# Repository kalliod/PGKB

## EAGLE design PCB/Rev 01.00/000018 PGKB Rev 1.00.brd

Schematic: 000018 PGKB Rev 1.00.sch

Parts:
C1, C2: C0805_18PF_50V_NP0; CAPC2012X160
C3, C4, C7, C8, C20, C46: C0805_1UF_50V_X5R; CAPC2012X160
C5, C9, C19, C21, C29, C30, C31, C33, C34, C44, C48: C0603_100NF_50V_X7R; CAPC1608X90
C6: C0805_10NF_50V_X7R; CAPC2012X160
C10, C11, C13, C14, C15, C16, C17, C18, C22, C23, C24, C25, C26, C27: C0805_1NF_50V_X7R; CAPC2012X160
C12: C0805_4.7UF_25V_X5R; CAPC2012X160
C28, C32: C1206_10UF_16V_Y5V; CAPC3216X200
D1: DIODE_TVS_5V_BI_824015; SOP95P280X120-6N
D2: DIODE_TVS_5V_SMAJ5.0A; DIOC530X280X230_SMA_A
D3: LED_0603_GREEN_CLEAR_APTD1608CGCK; LEDM1608X80N_DOME
D4, D27: LED_0603_AMBER_DIFF_LOQ976-PS-25; LEDM1608X80N
ENCLOSURE1: ENCLOSURE_BOPLA_BOP-500-9005-TOP; ENCLOSURE_BOPLA_BOP-500-9005
FB1, FB2, FB3, FB4, FB6: FERRITE_0805_0A5; RESC2012X50
FIDUCIAL1, FIDUCIAL2, FIDUCIAL3, FIDUCIAL4, FIDUCIAL5, FIDUCIAL6: FIDUCIAL
H1, H2, H3, H4, H5, H6, H7, H8: SWITCH_CAP_DSA_RELEG
L1: L_CHOKE_EXC-34CE670U; IND_CHOKE_EXC-34
LOGO2: ART_LOGO_TEXT_2.5MM-SILK; ART_LOGO_TEXT_2.5MM_SILK
R1, R7: R0805_10K_5%; RESC2012X50
R2, R3, R13, R18, R23, R25, R26, R27, R28, R29, R30: R0805_1K_1%; RESC2012X50
R4, R5: R0603_22; RESC1608X45N
R6: R0805_1M_5%; RESC2012X50
R8, R9, R10, R11, R12, R14, R15, R19, R21, R22, R31: R0805_200_1%; RESC2012X50
R16: R0402_DNP; RESC1005X35N
R17, R20: R0805_3K3_1%; RESC2012X50
R24, R32, R33: R0603_0; RESC1608X45N
S1, S3, S4, S5, S6, S7, S8, S9: SWITCH_BUTTON_MX1A-C1NW; SWITCH_BUTTON_CHERRY_MX
S10: SWITCH_MOM_SPST_FSM4JSMA; SWITCH_BUTTON_TE_FSM4JSMA
TP1, TP2, TP3, TP5, TP7, TP15, TP16, TP17: PAD_TEST_POINT-2.5/0.7_A; TEST_POINT_2.5MM_0.7HOLE_1SIDE
U1: IC_MCU_ATMEGA32U4-AU; QFP80P1000X1000X120-44R_N
U2: IC_MEM_FLASH_AT45DB321E; SOP127P800X175-8
U3: IC_REG_3V3_1A_NCP1117LPST33T3G; SOT223
U4, U5, U6: IC_LEVEL_SHIFTER_SN74LVC2T45; SOP65P400X130-8
X1: CON_USB_MICROB_UJ2-MIBH-4-SMT-TR-MAN; CON_USB_MICROB_UJ2-MIBH-4-SMT-TR_MAN
X2: CON_PROG_AVR_ISP-OFFSET_1X06; CON_PINHD_1X06_TH_OFFSET
X3: CON_1X04_TH_OFFSET_PADS-SILK; 1X04_TH_OFFSET
X4, X5, X6, X9, X10, X12, X17, X18: HOL_3.2/6.0_NP; MTG_NP_M3_320X600
X11: CON_MICROSD_MOLEX_5033981892-M; CON_MICROSD_MOLEX_5033981892_M
X13: PAD_TEST_GROUND_HOOK; PAD_GND_HOOK_M
X14: CON_CLAMP_PTSM_1X04_H_SMD; CON_PHOENIX_CONTACT_1702474
X15: CON_CLAMP_PTSM_1X08_H_SMD; CON_PHOENIX_CONTACT_1771088
Y1: OSC_CRYSTAL_16M_ABLS-16.000MHZ-B4-T-HC49; OSC_CRYSTAL_HC49/US

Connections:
!CS!_FLASH_3V3: U2.4 (!CS!), U6.6 (B2)
!CS!_FLASH_5V: U1.31 (PC6(OC3A/!OC4A!)), U6.3 (A2)
!CS!_SD_3V3: U6.7 (B1), X11.2 (CD/DAT3)
!CS!_SD_5V: U1.25 (PD4(ICP1/ADC8)), U6.2 (A1)
!RESET: R1.P$1 (1), S10.1, TP5.P$1, U1.13 (!RESET), X2.5 (RST), X3.1
!RESET!_3V3: R32.P$1 (1), U2.3 (!RESET!)
+3V3: C9.P$2 (2), C19.P$2 (2), C20.P$2 (2), C28.P$1 (1), C29.P$1 (1), C31.P$1 (1), C34.P$1 (1), C44.P$1 (1), C46.P$2 (2), R32.P$2 (2), R33.P$2 (2), TP3.P$1, U2.6 (V+), U3.2 (VO), U3.4 (VO), U4.8 (VB), U5.8 (VB), U6.8 (VB), X11.4 (VDD)
+5V: C3.P$1 (1), C4.P$1 (1), C5.P$1 (1), C6.P$1 (1), C12.P$1 (1), C21.P$2 (2), C30.P$2 (2), C32.P$1 (1), C33.P$2 (2), C48.P$1 (1), D1.5 (V+), D2.C (K), FB1.P$2 (2), FB3.P$1 (1), FB6.P$2 (2), R1.P$2 (2), R16.P$2 (2), R17.P$2 (2), R20.P$2 (2), R23.P$2 (2), TP7.P$1, U1.2 (UVCC), U1.14 (VCC), U1.34 (VCC1), U3.3 (VI), U4.1 (VA), U4.5 (DIR), U5.1 (VA), U6.1 (VA), U6.5 (DIR)
AD0: C22.P$1 (1), R25.P$2 (2), U1.36 (PF7(ADC7(TDI))
AD1: C23.P$1 (1), R26.P$2 (2), U1.37 (PF6(ADC6/TDO))
AD4: C24.P$1 (1), R27.P$2 (2), U1.38 (PF5(ADC5/TMS))
AD5: C25.P$1 (1), R28.P$2 (2), U1.39 (PF4(ADC4/TCK))
AD6: C26.P$1 (1), R29.P$2 (2), U1.40 (PF1(ADC1))
AD7: C27.P$1 (1), R30.P$2 (2), U1.41 (PF0(ADC0))
BUTTON1: C10.P$1 (1), R8.P$2 (2), U1.26 (PD6(T1/ADC9/!OC4D))
BUTTON2: C11.P$1 (1), R9.P$2 (2), U1.27 (PD7(OC4D/ADC10/T0))
BUTTON3: C13.P$1 (1), R10.P$2 (2), U1.28 (PB4(ADC11))
BUTTON4: C14.P$1 (1), R11.P$2 (2)
BUTTON5: C15.P$1 (1), R12.P$2 (2), U1.29 (PB5(OC1A/ADC12/!OC4B!))
BUTTON6: C16.P$1 (1), R14.P$2 (2), U1.30 (PB6(OC1B/OC4B/ADC13))
BUTTON7: C17.P$1 (1), R15.P$2 (2), U1.12 (PB7(OC0A/OC1C/RTS))
BUTTON8: C18.P$1 (1), R19.P$2 (2), U1.32 (PC7(ICP3/CLK0/OC4A))
CLK_3V3: TP1.P$1, U2.2 (SCK), U4.7 (B1), X11.5 (CLK)
CLK_5V: TP2.P$1, TP15.P$1, U1.9 (PB1(SCK)), U4.2 (A1), X2.3 (SCK)
GND: C1.P$2 (2), C2.P$2 (2), C3.P$2 (2), C4.P$2 (2), C5.P$2 (2), C6.P$2 (2), C7.P$2 (2), C9.P$1 (1), C10.P$2 (2), C11.P$2 (2), C12.P$2 (2), C13.P$2 (2), C14.P$2 (2), C15.P$2 (2), C16.P$2 (2), C17.P$2 (2), C18.P$2 (2), C19.P$1 (1), C20.P$1 (1), C21.P$1 (1), C22.P$2 (2), C23.P$2 (2), C24.P$2 (2), C25.P$2 (2), C26.P$2 (2), C27.P$2 (2), C28.P$2 (2), C29.P$2 (2), C30.P$1 (1), C31.P$2 (2), C32.P$2 (2), C33.P$1 (1), C34.P$2 (2), C44.P$2 (2), C46.P$1 (1), C48.P$2 (2), D2.A, D3.C (CATHODE), D4.C (CATHODE), D27.C (CATHODE), FB2.P$1 (1), FB4.P$1 (1), R7.P$2 (2), R24.P$2 (2), S1.1, S3.1, S4.1, S5.1, S6.1, S7.1, S8.1, S9.1, S10.3, U1.15 (GND), U1.23 (GND1), U1.35 (GND2), U1.43 (GND3), U2.7 (GND), U3.1 (GND), U4.4 (GND), U5.4 (GND), U5.5 (DIR), U6.4 (GND), X2.6 (GND), X3.4, X11.6 (VSS), X11.DET_LVR (LAT), X13.P$1, X13.P$2, X14.4, X15.8
GND_E: FB2.P$2 (2), X1.G1 (TAB), X1.G2 (TAB), X1.H1 (TAB), X1.H2 (TAB), X1.H3 (TAB), X1.H4 (TAB), X11.H1 (GND1), X11.H2 (GND2), X11.H3 (GND3), X11.H4 (GND4)
INTERRUPT7: R31.P$2 (2), U1.1 (PE6(INT.6/AIN0))
MISO_3V3: U2.8 (MISO), U5.7 (B1), X11.7 (DAT0)
MISO_5V: TP16.P$1, U1.11 (PB3(PDO/MISO)), U5.2 (A1), X2.1 (MISO)
MOSI_3V3: U2.1 (MOSI), U4.6 (B2), X11.3 (CMD)
MOSI_5V: TP17.P$1, U1.10 (PB2(PDI/MOSI)), U4.3 (A2), X2.4 (MOSI)
unnamed: D1.1, L1.A2, X1.D+
unnamed: D1.6, L1.B2, X1.D-
unnamed: C7.P$1 (1), FB3.P$2 (2), U1.24 (AVCC), U1.44 (AVCC1)
unnamed: D4.A (ANODE), R18.P$1 (1)
unnamed: C1.P$1 (1), R6.P$1 (1), U1.17 (XTAL1), Y1.2
unnamed: C2.P$1 (1), R6.P$2 (2), U1.16 (XTAL2), Y1.1
unnamed: C8.P$2 (2), U1.6 (UCAP)
unnamed: R2.P$2 (2), X3.2
unnamed: R3.P$2 (2), X3.3
unnamed: R7.P$1 (1), U1.33 (PE2(!HWB))
unnamed: D27.A (ANODE), R13.P$1 (1)
unnamed: R8.P$1 (1), S1.2
unnamed: R16.P$1 (1), X2.2 (VCC)
unnamed: R9.P$1 (1), S3.2
unnamed: R10.P$1 (1), S4.2
unnamed: R11.P$1 (1), S5.2
unnamed: R12.P$1 (1), S6.2
unnamed: R14.P$1 (1), S7.2
unnamed: R15.P$1 (1), S8.2
unnamed: R19.P$1 (1), S9.2
unnamed: L1.B1, R5.P$1 (1)
unnamed: L1.A1, R4.P$1 (1)
unnamed: R33.P$1 (1), U2.5 (!WP!)
unnamed: R17.P$1 (1), R21.P$1 (1), X14.1
unnamed: R20.P$1 (1), R22.P$1 (1), X14.2
unnamed: D3.A (ANODE), R23.P$1 (1)
unnamed: R24.P$1 (1), U5.6 (B2)
unnamed: FB6.P$1 (1), X15.1
unnamed: R27.P$1 (1), X15.4
unnamed: R28.P$1 (1), X15.5
unnamed: R31.P$1 (1), X14.3
unnamed: R25.P$1 (1), X15.2
unnamed: R26.P$1 (1), X15.3
unnamed: R29.P$1 (1), X15.6
unnamed: R30.P$1 (1), X15.7
RXD: R2.P$1 (1), U1.20 (PD2(INT2/RXD1))
RX_LED: R13.P$2 (2), U1.8 (PB0(SS))
SCL_5V: R21.P$2 (2), U1.18 (PD0(INT0/OC0B/SCL))
SDA_5V: R22.P$2 (2), U1.19 (PD1(INT1/SDA))
SD_DETECT: X11.DET_SW (SW)
TXD: R3.P$1 (1), U1.21 (PD3(INT3/TXD1))
TX_LED: R18.P$2 (2), U1.22 (PD5(XCK/CTS))
USB_D+: R4.P$2 (2), U1.4 (D+)
USB_D-: R5.P$2 (2), U1.3 (D-)
USB_GND: C8.P$1 (1), D1.2 (V-), FB4.P$2 (2), U1.5 (UGND), X1.GND
USB_ID: X1.ID
USB_VBUS: FB1.P$1 (1), U1.7 (VBUS), X1.VBUS (V+)

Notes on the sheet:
Fiducials
Artwork
Mounting screws (optional)
Ground loop
microSD card slot
Programming connectors
!RESET! signal
3V3 regulation
USB connector
SPI bus level shifting
GND
Microcontroller
USB data LED
Buttons
Flash memory chip
External I2C connector
// D2 SDA
// D3 SCL
// A0
// A1
// A4
// A5
// A6
// A7
// USB data LED
Power LED
ADC
Use internal 2.56 V ref
// D7
// D0 RX
// D1 TX
// D4
// D12
// D13
// D6
// D8
// D9
// D10
// D11
// D5

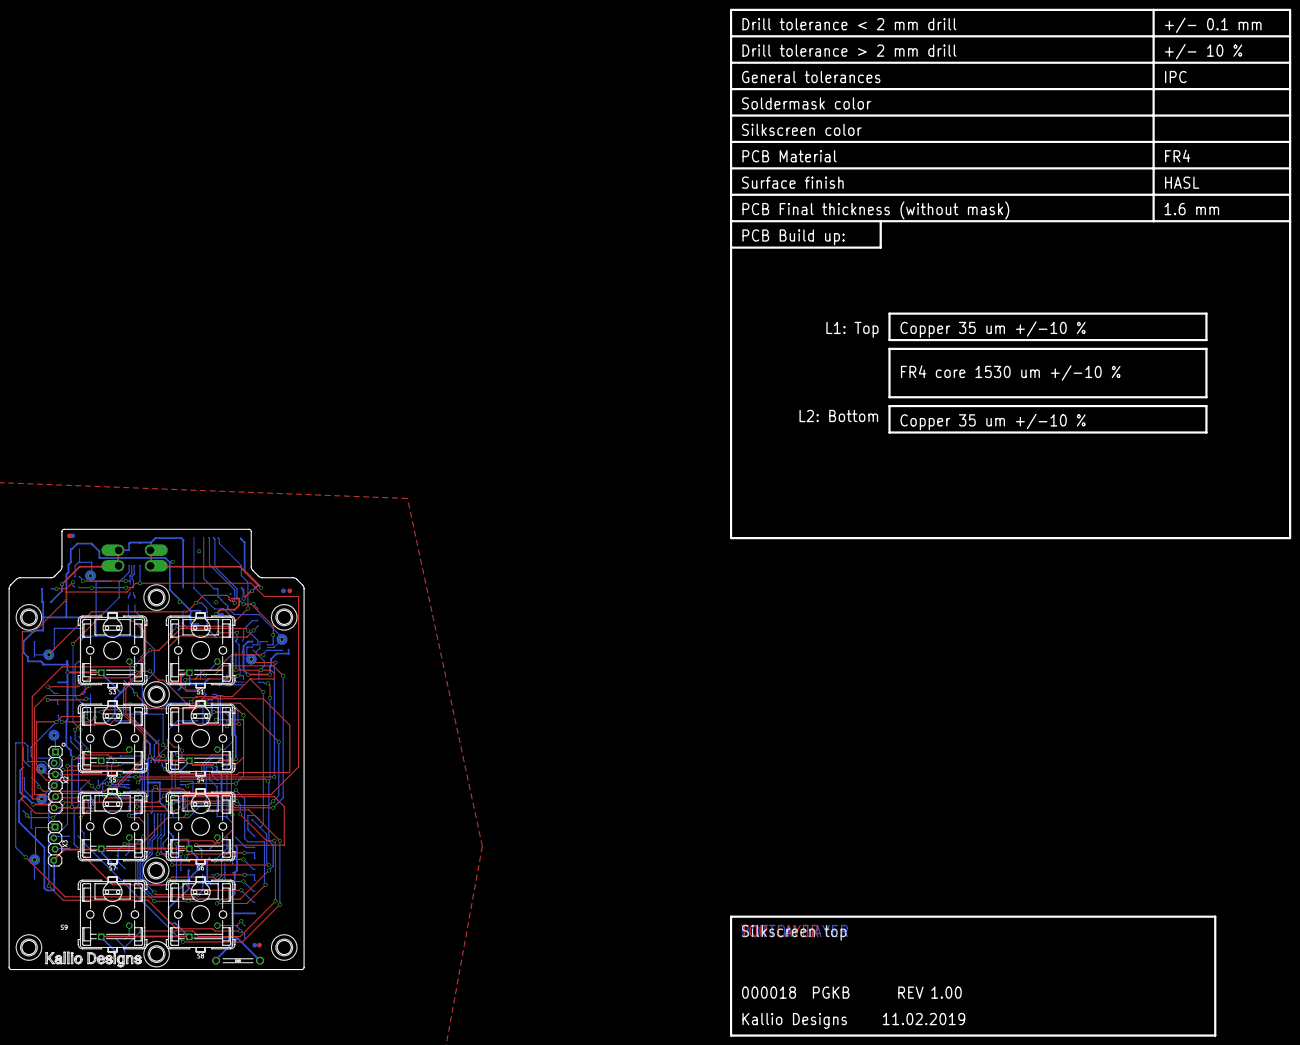
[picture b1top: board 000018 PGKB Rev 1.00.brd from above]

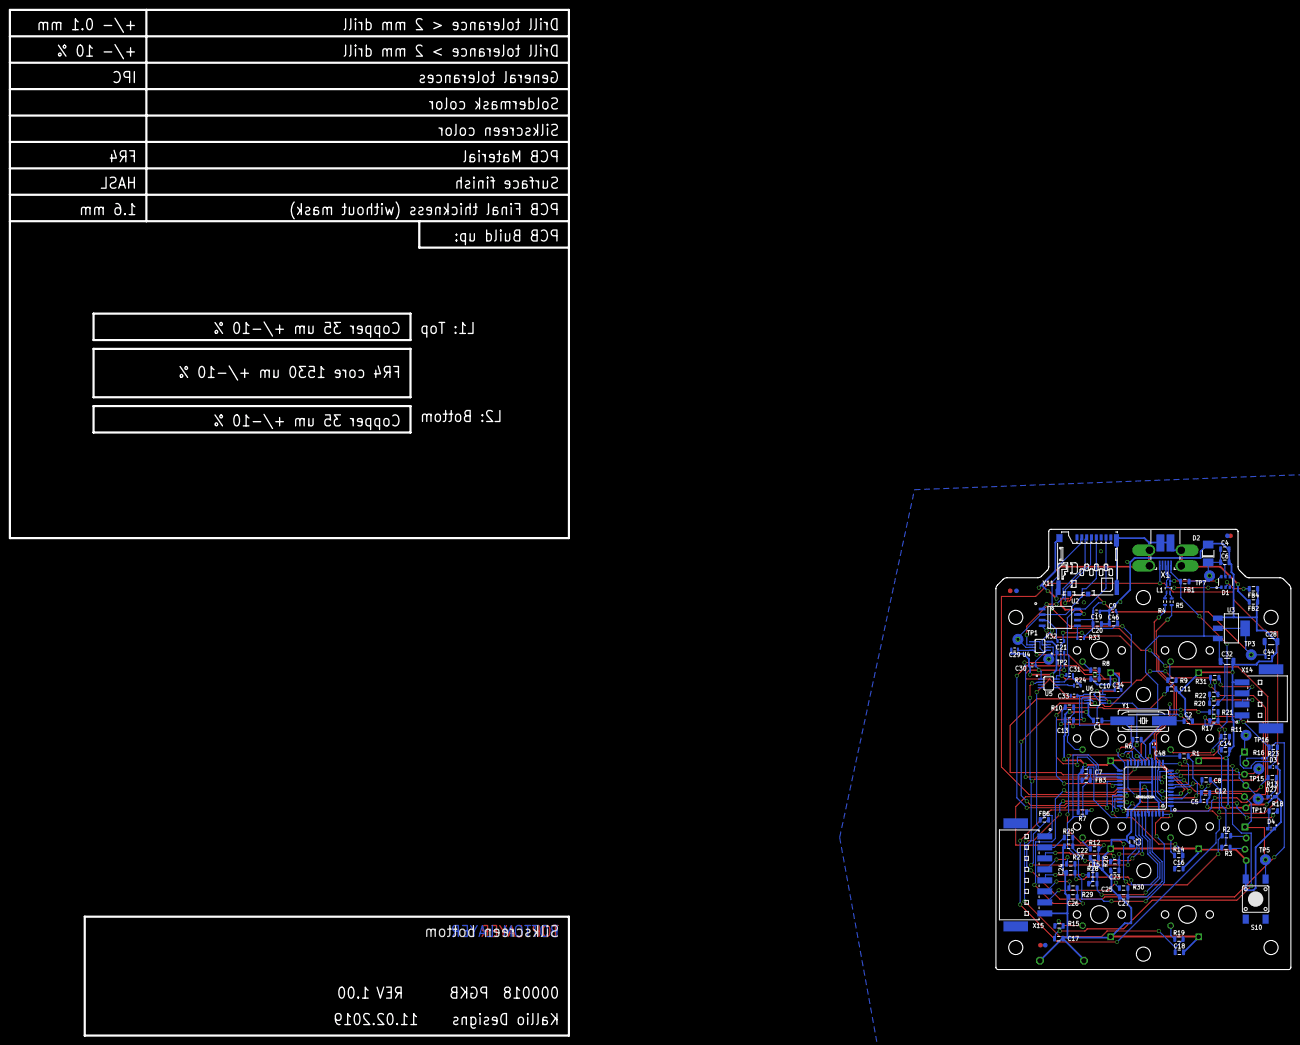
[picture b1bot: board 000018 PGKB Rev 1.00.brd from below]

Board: 2 copper layers, 290.8 x 233.0 mm, 136 parts (104 on the bottom side), 76 nets.

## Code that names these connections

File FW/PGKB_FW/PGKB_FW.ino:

#include <Wire.h>
#include "Adafruit_MCP23017.h"
#include "KD_ardu_button.h"
#include <Keyboard.h>

/* Hardware configuration */

// TL: My keyboard writes 900 characters if a key is pressed for 30 sec. If
// two keys are pressed the amount of characters is doubled

// HW
#define BUTTON_DEBOUNCE 20                          // button debounce (ms)
#define NO_OF_BUTTONS 8

// ADC
#define AUX_VREF 2.56
#define ADC_CHANNELS 1024

/* Define debugging level */

// Doesn't work too well with serial port and HID enabled
#define DEBUG_LEVEL 0
#define POST_INTERVAL 5000

/* Serial port */

#define SERIAL_BAUD_RATE 57600                      // 57600 max with internal 8 MHz oscillator

/* Keyboard layout */

#define KB_LAYOUT_FI

/***********************************************************************************************************************/
/*                                                  pin definitions                                                    */
/***********************************************************************************************************************/

/* Arduino digital */
const int button1_pin = 12;
const int button2_pin = 6;
const int button3_pin = 8;
const int button4_pin = 0;   // NOT CONNECTED IN PCB REV 1.00
const int button5_pin = 9;
const int button6_pin = 10;
const int button7_pin = 11;
const int button8_pin = 13;

const int interrupt7_pin = 7;

//const int rx_led_pin = ??; // ARE THESE HW FUNCTIONS?
//const int tx_led_pin = 4;

/* Arduino analog */
const int analog0 = 14;
const int analog1 = 15;
//const int analog2 = 16;     // NOT IN USE
//const int analog3 = 17;     // NOT IN USE
const int analog4 = 18;
const int analog5 = 19;
//const int analog6 = 20;     // WHICH PIN?
//const int analog7 = 21;     // WHICH PIN?

/***********************************************************************************************************************/
/*                                                   VARIABLES                                                         */
/***********************************************************************************************************************/

/* Other variables */

// pin, pullup, inverted
Button onb_button[NO_OF_BUTTONS];

// Debugging
unsigned long _last_post_time = 0;
byte cycle_count = 0;

// Keyboard
bool b_pressed[NO_OF_BUTTONS];
char b_char[NO_OF_BUTTONS][2];

/***********************************************************************************************************************/
/*                                                   FUNCTIONS                                                         */
/***********************************************************************************************************************/

/* Analog in */
float read_voltage();

/***********************************************************************************************************************/
/*                                                   SETUP LOOP                                                        */
/***********************************************************************************************************************/

void setup() {

/* Keyboard layout */
// compare to US Apple Macintosh keyboard layout

#ifdef KB_LAYOUT_US
  b_char[0][0] = '\0';
  b_char[0][1] = ')';
  b_char[1][0] = '\0';
  b_char[1][1] = '(';
  b_char[2][0] = '\0';
  b_char[2][1] = '}';
  b_char[3][0] = '\0';
  b_char[3][1] = '{';
  b_char[4][0] = '\0';
  b_char[4][1] = ']';
  b_char[5][0] = '\0';
  b_char[5][1] = '[';
  b_char[6][0] = '\0';
  b_char[6][1] = '"';
  b_char[7][0] = '\0';
  b_char[7][1] = '\'';
#endif

#ifdef KB_LAYOUT_FI
  b_char[0][0] = KEY_LEFT_SHIFT;
  b_char[0][1] = '9';
  b_char[1][0] = KEY_LEFT_SHIFT;
  b_char[1][1] = '8';
  b_char[2][0] = KEY_RIGHT_ALT;
  b_char[2][1] = '0';
  b_char[3][0] = KEY_RIGHT_ALT;
  b_char[3][1] = '7';
  b_char[4][0] = KEY_RIGHT_ALT;
  b_char[4][1] = '9';
  b_char[5][0] = KEY_RIGHT_ALT;
  b_char[5][1] = '8';
  b_char[6][0] = KEY_LEFT_SHIFT;
  b_char[6][1] = '2';
  b_char[7][0] = '\0';
  b_char[7][1] = '\\';
#endif

  // ADC
  analogReference(INTERNAL);

  /* Pin settings on Arduino */

  // pins
  pinMode(interrupt7_pin, INPUT_PULLUP);

  onb_button[0].setPin(button1_pin);
  onb_button[1].setPin(button2_pin);
  onb_button[2].setPin(button3_pin);
  onb_button[3].setPin(button4_pin);
  onb_button[4].setPin(button5_pin);
  onb_button[5].setPin(button6_pin);
  onb_button[6].setPin(button7_pin);
  onb_button[7].setPin(button8_pin);
  
  for (int i = 0; i < NO_OF_BUTTONS; i++){
    b_pressed[i] = false;
  }

  for (int i = 0; i < NO_OF_BUTTONS; i++){
    onb_button[i].setPullup(HIGH);
    onb_button[i].setInverted(HIGH);
  }

  // Keyboard
  Keyboard.begin();

  /* Serial communications setup */
#if DEBUG_LEVEL > 1
  Serial.begin(SERIAL_BAUD_RATE);
  while(!Serial){
    ;                                               // Needed for Atmega32U4
  }  
#endif

#if DEBUG_LEVEL > 1
  Serial.println(F("Serial port opened"));
  Serial.print(F("Serial baud rate: "));
  Serial.print(SERIAL_BAUD_RATE);
  Serial.println(F(" bit/s"));
#endif

  /* Setup complete */

#if DEBUG_LEVEL > 1
  Serial.println(F("Setup complete"));
#endif
  
}

/***********************************************************************************************************************/
/*                                                   MAIN LOOP                                                         */
/***********************************************************************************************************************/

void loop() {

  for (int i = 0; i < 8; i++) {
    if (onb_button[i].pressed()) {
      delay(BUTTON_DEBOUNCE);
      if(onb_button[i].state()) {
#if DEBUG_LEVEL > 3
        Serial.print(F("pressed key: "));
        Serial.println(i+1);
#endif
        for (int j = 0; j < 2; j++) {
          Keyboard.press(b_char[i][j]);
        }
        b_pressed[i] = true;
      }

    } else if (b_pressed[i] && onb_button[i].isReleased()) {
      delay(BUTTON_DEBOUNCE);
      b_pressed[i] = false;
#if DEBUG_LEVEL > 3
      Serial.print(F("released key: "));
      Serial.println(i+1);
#endif
      Keyboard.releaseAll();
    }
  }

// Debugging
#if DEBUG_LEVEL > 6
    if((_last_post_time + POST_INTERVAL) < millis())
    {
      // Debug info
      Serial.println(F("debugging info:"));
      Serial.print(F("Cycle: "));
      Serial.println(cycle_count);

      _last_post_time = millis();
      cycle_count++;
      Serial.println("------");
  }
#endif
} // void loop()

/* Analog in */
float read_voltage() {
  float _result = 0;
  _result = AUX_VREF * analogRead(A1) / ADC_CHANNELS;
  return _result;
}

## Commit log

2019-04-06 Import libraries
2019-04-06 Initial
2019-04-06 First tests
    Works fine for two keys
2019-04-06 Country variants and buttons as array
    Can't really use modifier keys
2019-04-06 Added modifier keys
    Worked fine for a while, but started to give 9 presses at once
2019-04-06 Bugfix
    All good again Finnish layout defined
2023-10-08 Rev 2 schematic started
2023-10-08 buttons
2023-10-08 cleanup
2023-10-12 schematic
2023-10-15 ledit
2023-10-15 skema
2023-10-16 Layout
2023-10-17 Board outline update
2023-10-17 step
2023-10-17 sitte vaan routaus
2023-10-17 4L board
2023-10-18 Leiskaa
2023-10-19 error fixing
2023-10-20 päivityksiä
2023-10-22 Review checklists
2023-10-23 USB connector moved
2023-10-27 Button support
2023-10-27 PN added
2024-01-24 mfg files
2024-01-24 MODIFICATIONS To Rev 2
2024-01-24 MODIFICATIONS Updates
2024-02-03 RPi keyboard FW
2024-02-10 file rename
2024-04-08 Updates started
2024-05-04 Maybe new psu needed
2024-07-14 Bugfixes for Rev 2
    Oscillator, USB reversed, USB series resistors values
2024-07-14 File version update
2024-07-14 Update USBcon.kicad_sch
    Changed back to 0603 components
2024-07-14 Updated layout from schematic
2024-07-14 routed all
2024-07-14 Resolved DRC problems
2024-07-15 Test points for encoder signals
2024-07-15 Update PKGBV2.ino
    Ehkä tän pitäis toimia paremmin näin?
2024-07-15 Encoder Test points to layout
2024-07-16 Signals renamed
2024-07-16 Nappi- ja neopixel-testausta
2024-07-16 GND hook added
2024-08-18 Rev3 outputs
2024-08-26 STL generated
2024-08-26 update stl
2024-11-11 SW updates
2025-01-06 Rev 3 tekemista
2025-01-08 mfg outputs
